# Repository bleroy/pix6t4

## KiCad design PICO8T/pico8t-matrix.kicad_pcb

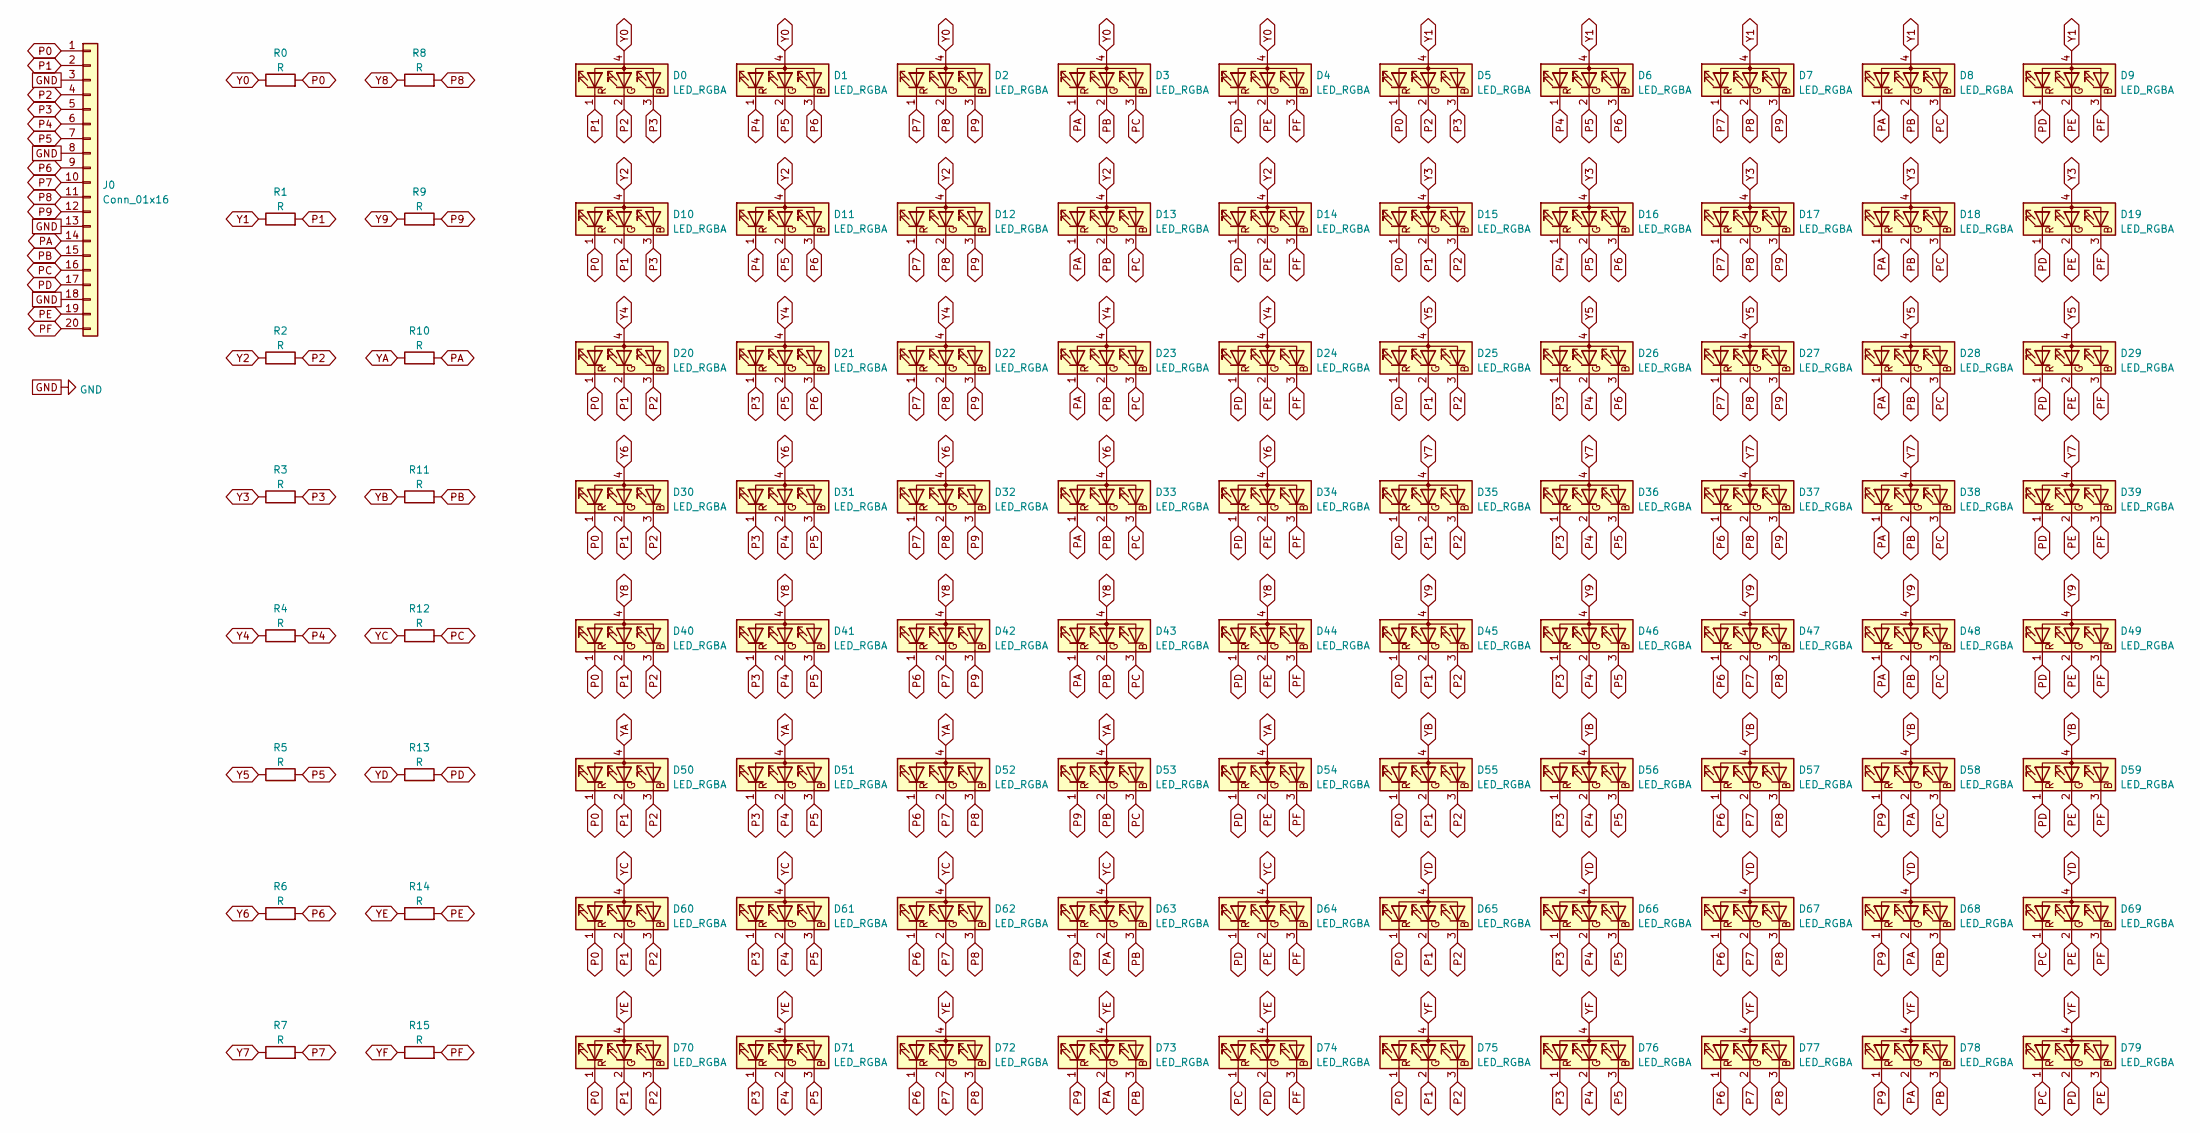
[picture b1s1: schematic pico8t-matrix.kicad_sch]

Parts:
D0, D1, D2, D3, D4, D5, D6, D7, D8, D9, D10, D11, D12, D13, D14, D15, D16, D17, D18, D19, D20, D21, D22, D23, D24, D25, D26, D27, D28, D29, D30, D31, D32, D33, D34, D35, D36, D37, D38, D39, D40, D41, D42, D43, D44, D45, D46, D47, D48, D49, D50, D51, D52, D53, D54, D55, D56, D57, D58, D59, D60, D61, D62, D63, D64, D65, D66, D67, D68, D69, D70, D71, D72, D73, D74, D75, D76, D77, D78, D79: LED_RGBA; RGB_LED
J0: Conn_01x16; PinHeader_1x20_P2.54mm_Vertical
R0, R1, R2, R3, R4, R5, R6, R7, R8, R9, R10, R11, R12, R13, R14, R15: R; R_0603_1608Metric_Pad0.98x0.95mm_HandSolder

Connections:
GND: J0.3, J0.8, J0.13, J0.18
P0: D5.1 (RK), D10.1 (RK), D15.1 (RK), D20.1 (RK), D25.1 (RK), D30.1 (RK), D35.1 (RK), D40.1 (RK), D45.1 (RK), D50.1 (RK), D55.1 (RK), D60.1 (RK), D65.1 (RK), D70.1 (RK), D75.1 (RK), J0.1, R0.2
P1: D0.1 (RK), D10.2 (GK), D15.2 (GK), D20.2 (GK), D25.2 (GK), D30.2 (GK), D35.2 (GK), D40.2 (GK), D45.2 (GK), D50.2 (GK), D55.2 (GK), D60.2 (GK), D65.2 (GK), D70.2 (GK), D75.2 (GK), J0.2, R1.2
P2: D0.2 (GK), D5.2 (GK), D15.3 (BK), D20.3 (BK), D25.3 (BK), D30.3 (BK), D35.3 (BK), D40.3 (BK), D45.3 (BK), D50.3 (BK), D55.3 (BK), D60.3 (BK), D65.3 (BK), D70.3 (BK), D75.3 (BK), J0.4, R2.2
P3: D0.3 (BK), D5.3 (BK), D10.3 (BK), D21.1 (RK), D26.1 (RK), D31.1 (RK), D36.1 (RK), D41.1 (RK), D46.1 (RK), D51.1 (RK), D56.1 (RK), D61.1 (RK), D66.1 (RK), D71.1 (RK), D76.1 (RK), J0.5, R3.2
P4: D1.1 (RK), D6.1 (RK), D11.1 (RK), D16.1 (RK), D26.2 (GK), D31.2 (GK), D36.2 (GK), D41.2 (GK), D46.2 (GK), D51.2 (GK), D56.2 (GK), D61.2 (GK), D66.2 (GK), D71.2 (GK), D76.2 (GK), J0.6, R4.2
P5: D1.2 (GK), D6.2 (GK), D11.2 (GK), D16.2 (GK), D21.2 (GK), D31.3 (BK), D36.3 (BK), D41.3 (BK), D46.3 (BK), D51.3 (BK), D56.3 (BK), D61.3 (BK), D66.3 (BK), D71.3 (BK), D76.3 (BK), J0.7, R5.2
P6: D1.3 (BK), D6.3 (BK), D11.3 (BK), D16.3 (BK), D21.3 (BK), D26.3 (BK), D37.1 (RK), D42.1 (RK), D47.1 (RK), D52.1 (RK), D57.1 (RK), D62.1 (RK), D67.1 (RK), D72.1 (RK), D77.1 (RK), J0.9, R6.2
P7: D2.1 (RK), D7.1 (RK), D12.1 (RK), D17.1 (RK), D22.1 (RK), D27.1 (RK), D32.1 (RK), D42.2 (GK), D47.2 (GK), D52.2 (GK), D57.2 (GK), D62.2 (GK), D67.2 (GK), D72.2 (GK), D77.2 (GK), J0.10, R7.2
P8: D2.2 (GK), D7.2 (GK), D12.2 (GK), D17.2 (GK), D22.2 (GK), D27.2 (GK), D32.2 (GK), D37.2 (GK), D47.3 (BK), D52.3 (BK), D57.3 (BK), D62.3 (BK), D67.3 (BK), D72.3 (BK), D77.3 (BK), J0.11, R8.2
P9: D2.3 (BK), D7.3 (BK), D12.3 (BK), D17.3 (BK), D22.3 (BK), D27.3 (BK), D32.3 (BK), D37.3 (BK), D42.3 (BK), D53.1 (RK), D58.1 (RK), D63.1 (RK), D68.1 (RK), D73.1 (RK), D78.1 (RK), J0.12, R9.2
PA: D3.1 (RK), D8.1 (RK), D13.1 (RK), D18.1 (RK), D23.1 (RK), D28.1 (RK), D33.1 (RK), D38.1 (RK), D43.1 (RK), D48.1 (RK), D58.2 (GK), D63.2 (GK), D68.2 (GK), D73.2 (GK), D78.2 (GK), J0.14, R10.2
PB: D3.2 (GK), D8.2 (GK), D13.2 (GK), D18.2 (GK), D23.2 (GK), D28.2 (GK), D33.2 (GK), D38.2 (GK), D43.2 (GK), D48.2 (GK), D53.2 (GK), D63.3 (BK), D68.3 (BK), D73.3 (BK), D78.3 (BK), J0.15, R11.2
PC: D3.3 (BK), D8.3 (BK), D13.3 (BK), D18.3 (BK), D23.3 (BK), D28.3 (BK), D33.3 (BK), D38.3 (BK), D43.3 (BK), D48.3 (BK), D53.3 (BK), D58.3 (BK), D69.1 (RK), D74.1 (RK), D79.1 (RK), J0.16, R12.2
PD: D4.1 (RK), D9.1 (RK), D14.1 (RK), D19.1 (RK), D24.1 (RK), D29.1 (RK), D34.1 (RK), D39.1 (RK), D44.1 (RK), D49.1 (RK), D54.1 (RK), D59.1 (RK), D64.1 (RK), D74.2 (GK), D79.2 (GK), J0.17, R13.2
PE: D4.2 (GK), D9.2 (GK), D14.2 (GK), D19.2 (GK), D24.2 (GK), D29.2 (GK), D34.2 (GK), D39.2 (GK), D44.2 (GK), D49.2 (GK), D54.2 (GK), D59.2 (GK), D64.2 (GK), D69.2 (GK), D79.3 (BK), J0.19, R14.2
PF: D4.3 (BK), D9.3 (BK), D14.3 (BK), D19.3 (BK), D24.3 (BK), D29.3 (BK), D34.3 (BK), D39.3 (BK), D44.3 (BK), D49.3 (BK), D54.3 (BK), D59.3 (BK), D64.3 (BK), D69.3 (BK), D74.3 (BK), J0.20, R15.2
Y0: D0.4 (A), D1.4 (A), D2.4 (A), D3.4 (A), D4.4 (A), R0.1
Y1: D5.4 (A), D6.4 (A), D7.4 (A), D8.4 (A), D9.4 (A), R1.1
Y2: D10.4 (A), D11.4 (A), D12.4 (A), D13.4 (A), D14.4 (A), R2.1
Y3: D15.4 (A), D16.4 (A), D17.4 (A), D18.4 (A), D19.4 (A), R3.1
Y4: D20.4 (A), D21.4 (A), D22.4 (A), D23.4 (A), D24.4 (A), R4.1
Y5: D25.4 (A), D26.4 (A), D27.4 (A), D28.4 (A), D29.4 (A), R5.1
Y6: D30.4 (A), D31.4 (A), D32.4 (A), D33.4 (A), D34.4 (A), R6.1
Y7: D35.4 (A), D36.4 (A), D37.4 (A), D38.4 (A), D39.4 (A), R7.1
Y8: D40.4 (A), D41.4 (A), D42.4 (A), D43.4 (A), D44.4 (A), R8.1
Y9: D45.4 (A), D46.4 (A), D47.4 (A), D48.4 (A), D49.4 (A), R9.1
YA: D50.4 (A), D51.4 (A), D52.4 (A), D53.4 (A), D54.4 (A), R10.1
YB: D55.4 (A), D56.4 (A), D57.4 (A), D58.4 (A), D59.4 (A), R11.1
YC: D60.4 (A), D61.4 (A), D62.4 (A), D63.4 (A), D64.4 (A), R12.1
YD: D65.4 (A), D66.4 (A), D67.4 (A), D68.4 (A), D69.4 (A), R13.1
YE: D70.4 (A), D71.4 (A), D72.4 (A), D73.4 (A), D74.4 (A), R14.1
YF: D75.4 (A), D76.4 (A), D77.4 (A), D78.4 (A), D79.4 (A), R15.1

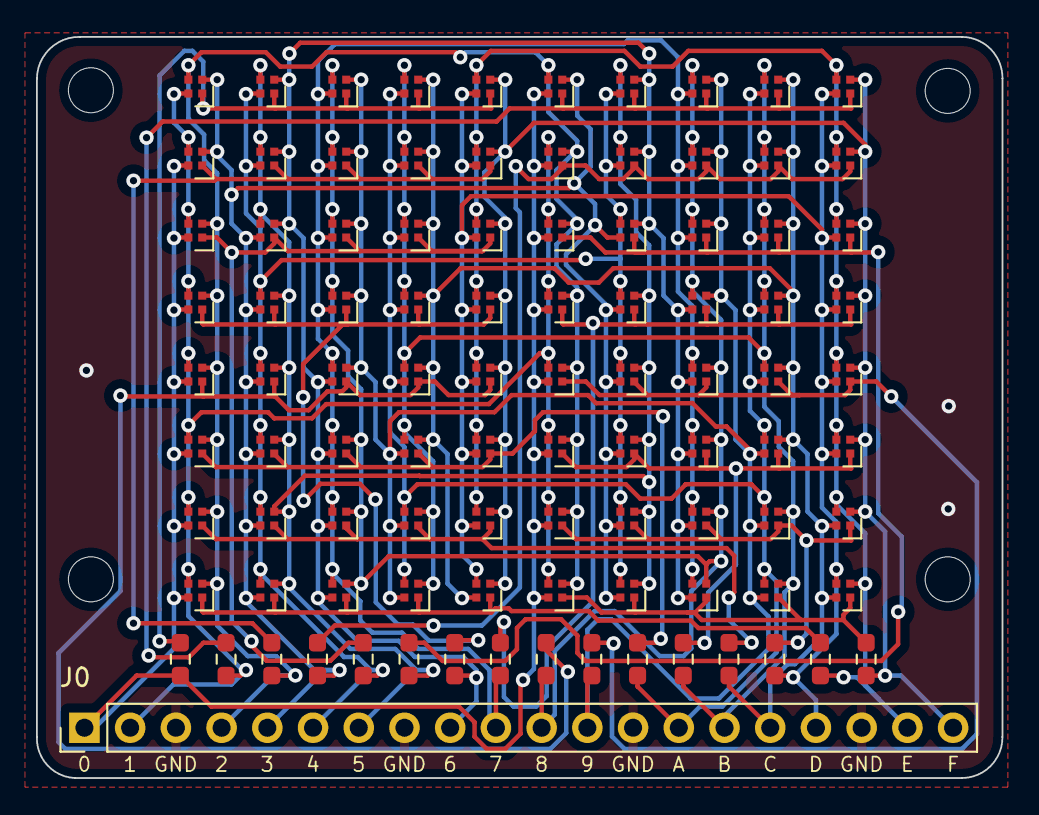
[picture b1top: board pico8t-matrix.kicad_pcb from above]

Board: 2 copper layers, 53.6 x 41.2 mm, 97 parts (0 on the bottom side), 33 nets.

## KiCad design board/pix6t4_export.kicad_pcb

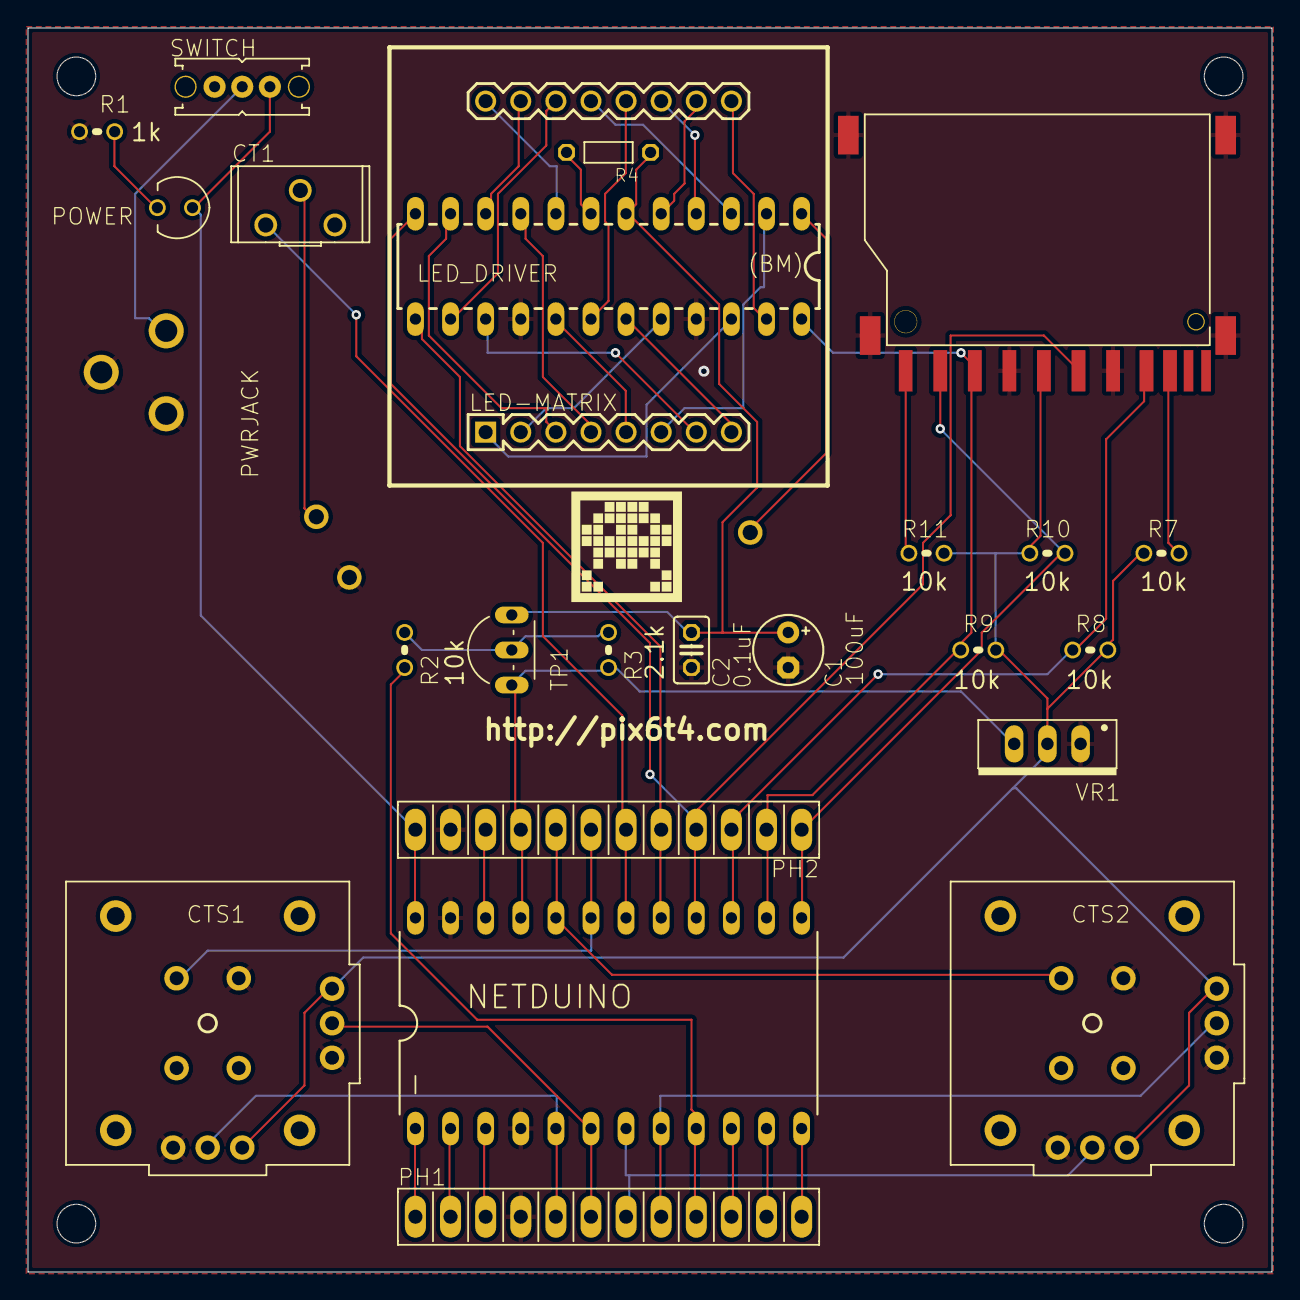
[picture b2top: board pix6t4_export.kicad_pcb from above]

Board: 2 copper layers, 90.0 x 90.0 mm, 32 parts (0 on the bottom side), 49 nets.

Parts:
@HOLE0, @HOLE1, @HOLE2, @HOLE3: (no value)
C1: 100uF; E2,5-5
C2: 0.1uF; C025-025X050
CT1: CB10HL; CARBONTRIMMER
CTS1, CTS2: CTS252B103A60NB10K; JOYSTICK+SWITCH
GND: WIREPAD
LED-MATRIX: LEDMS88R-V2SQR; LEDMATRIX-SQRPIXELS
LED_DRIVER: LED-DRIVER-BOTTOM-MOUNT; DIL24-BOTTOM-MOUNT
NETDUINO: NETDUINO-MINI-V2; NETDUINO-MINI
PH1, PH2: PINHEADER1X12BREAKAWAY; PINHEADER
POWER: LED; LED3MM
PWRJACK: PJ-102A-V2; DCBARREL
R1: 1k; RESISTOR
R2, R7, R8, R9, R10, R11: 10k; RESISTOR
R3: 2.1k; RESISTOR
R4: RESISTOR-FLAT
SD-SOCKET: SD-101-00708-64-ND-V3; SMD-SD-SOCKET
SWITCH: SLIDE-SWITCH-V2; SLIDE-SWITCH
TP1: 2N4403TO-92; TRANSISTOR-PNP
U$1, U$3: WIREPAD
VR1: VREG-LD33VT0-220; VOLTAGEREGULATOR

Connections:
+3V3: CTS1.H+, CTS1.V+, CTS2.H+, CTS2.V+, R7.1, R8.1, R9.1, R10.1, R11.1, SD-SOCKET.4-VDD-3.3V, VR1.VOUT
+5.0V: NETDUINO.21, PH2.9, R3.2, TP1.E, VR1.VIN
+VIN: NETDUINO.24, PH2.12, POWER.A, SWITCH.CLOSED
GND: C1.-, C2.2, CTS1.H-, CTS1.SEL-, CTS1.V-, CTS2.H-, CTS2.SEL-, CTS2.V-, GND.P$1, LED_DRIVER.4BM, LED_DRIVER.9BM, NETDUINO.4, NETDUINO.23, PH1.4, PH2.11, PWRJACK.GND, PWRJACK.GNDBREAK, R1.2, SD-SOCKET.3-VSS-GND, SD-SOCKET.6-VSS-GND, SD-SOCKET.GND0, SD-SOCKET.GND1, SD-SOCKET.GND2, SD-SOCKET.GND3, VR1.GND
LED_DRIVER_CURRENT_LIMIT: LED_DRIVER.18BM, R4.2
LED_DRIVER_DATA_OUT: LED_DRIVER.24BM, U$1.P$1
LED_DRIVER_POWER: C1.+, C2.1, LED_DRIVER.19BM, R4.1, TP1.C
LED_DRIVER_POWER_CTRL: NETDUINO.9, PH1.9, R2.1
LED_DRIVER_SPI_CS: LED_DRIVER.12BM, NETDUINO.17, PH2.5
LED_PIN_1: LED-MATRIX.1, LED_DRIVER.3BM
LED_PIN_2: LED-MATRIX.2, LED_DRIVER.5BM
LED_PIN_3: LED-MATRIX.3, LED_DRIVER.14BM
LED_PIN_4: LED-MATRIX.4, LED_DRIVER.16BM
LED_PIN_5: LED-MATRIX.5, LED_DRIVER.8BM
LED_PIN_6: LED-MATRIX.6, LED_DRIVER.23BM
LED_PIN_7: LED-MATRIX.7, LED_DRIVER.10BM
LED_PIN_8: LED-MATRIX.8, LED_DRIVER.6BM
LED_PIN_9: LED-MATRIX.9, LED_DRIVER.2BM
LED_PIN_10: LED-MATRIX.10, LED_DRIVER.20BM
LED_PIN_11: LED-MATRIX.11, LED_DRIVER.21BM
LED_PIN_12: LED-MATRIX.12, LED_DRIVER.7BM
LED_PIN_13: LED-MATRIX.13, LED_DRIVER.22BM
LED_PIN_14: LED-MATRIX.14, LED_DRIVER.11BM
LED_PIN_15: LED-MATRIX.15, LED_DRIVER.15BM
LED_PIN_16: LED-MATRIX.16, LED_DRIVER.17BM
LEFT_STICK_BUTTON: CTS1.SEL+, NETDUINO.19, PH2.7
LEFT_STICK_X: CTS1.H-OUT, NETDUINO.5, PH1.5
LEFT_STICK_Y: CTS1.V-OUT, NETDUINO.6, PH1.6
unnamed: POWER.K, R1.1
unnamed: R7.2, SD-SOCKET.8-DAT1-IRQ-RSV
unnamed: NETDUINO.1, PH1.1
unnamed: R11.2, SD-SOCKET.9-DAT2-RSV
unnamed: NETDUINO.2, PH1.2
unnamed: NETDUINO.3, PH1.3
unnamed: R2.2, R3.1, TP1.B
unnamed: NETDUINO.12, PH1.12
unnamed: NETDUINO.11, PH1.11
unnamed: NETDUINO.10, PH1.10
unnamed: CT1.VOUT, U$3.P$1
PWR: PWRJACK.PWR, SWITCH.PWR
RESET: NETDUINO.22, PH2.10
RIGHT_STICK_BUTTON: CTS2.SEL+, NETDUINO.20, PH2.8
RIGHT_STICK_X: CTS2.H-OUT, NETDUINO.7, PH1.7
RIGHT_STICK_Y: CTS2.V-OUT, NETDUINO.8, PH1.8
SPEAKER: CT1.VIN, NETDUINO.18, PH2.6
SPI_CLK: LED_DRIVER.13BM, NETDUINO.16, PH2.4, SD-SOCKET.5-CLK
SPI_MISO: NETDUINO.15, PH2.3, R8.2, SD-SOCKET.7-DAT0-DO-MISO
SPI_MOSI: LED_DRIVER.1BM, NETDUINO.14, PH2.2, R9.2, SD-SOCKET.2-CMD-DI-MOSI
SPI_SD_CS: NETDUINO.13, PH2.1, R10.2, SD-SOCKET.1-CD-DAT3-CS

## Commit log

2023-02-02 Fix RGB LED footprint
2023-02-02 Update ignored files
2023-03-16 Matrix8T revision with first driver
2023-03-16 Schematic SVG

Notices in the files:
PICO8T/pico8t-matrix.kicad_pcb:
© Bertrand Le Roy 2023
